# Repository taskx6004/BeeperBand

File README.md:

# BeeperBand

The BeeperBand is an open hardware project to build a minimalist wrist band to notify smartphone message notification with haptic, RGB lights, and interact with physical buttons via BLE connection.

Current prototype intentionally not fitting any display, there are only 3 RGB LEDs, for visual indications. A Linear Haptic Driver can notify user with patterned vibration with minimum audible noise, for non-intrusive usage in various social occasions.

The hardware design is a basically a re-layout PCB of a Adafruit nRF52 Express, to minimize initial firmware development efforts. It also has more sophisticated charger, peripherals required by project specs, and various design decisions for power saving and MCU IO voltage level translations, to utilize software configurable voltage features of nRF52 integrated power converters.

## System Design

nRF52840 is a 2.4GHz RFIC with integrated power converters and flexible IO mapping, with USB2.0 full speed PHY, but has no DFU rom(will brake when no proper firmware present). It can be powered directly with USB host or Li-ion battery, with two stage convert, or single stage convert (skipping first high voltage conversion); two stage conversion could both choose between integrated LDO or buck converter, while buck converter require extra inductors and capacitors to be functional.

To maximize battery life, the BeeperBand implemented two stage buck converter design, all peripheral I/Os have dedicated level translation, and core of nRF52840 works on default 1.8v.

Current stage there’s no functional firmware for BeeperBand hardware (v0.41), all testing is done with Adafruit Feather nRF52840 express bootloader and accompanying BSP and Arduino.

## Peripherals

- 6 GPIO buttons, low-active (enabled when connected to GND)
- 3 x RGB LEDs, SW2812 serial protocol, daisy chained
  - powered by dedicated 3.3V buck converter, with EN pin
  - buck converter is powered by battery
- 1x Linear Haptic Driver
  - dedicated level transfer chip for I2C and GPIO
  - powered by battery, wide voltage range tolerate by level translation
- All unused IO fanned out by 30pin B2B connector
  - with battery output pins
  - 20 IO pins
- 2 LEDs, inherent from Adafruit nRF52840 Feather Express Design
  - RED for Arduino serial activity
  - BLUE for BLE connection activity
  - testing purpose, so the brightness is set to very low (1k resistor on 1.8V IO)

## Charger Circuit

Charger chip is BQ25619 from Texas Instrument with QFN footprint. A WLCSP footprint version is available with part# BQ25618. If PCB size requires further miniaturization, charger and MCU chip can  both replaced with software compatible WLCSP (0.4mm pitch BGA) footprint version.

Like many other BQ chargers from TI, it has a register map for extensive internal controls. But preliminary charging functions does no require MCU control presents. The I/O pins connected to the charger are unused in Feather Express design, so application developer can ignore its presents. To reach 4.2V charge voltage (default 4.1V), and charging current control, a driver firmware is required, and it will work with no intervention to application programs. The power source transition between charging and battery is also seamless, with no program control needed.

BQ chip has 4 power terminals, a little back ground may be helpful in first encounter.

- USB input (VBUS)
  - charge power input
- USB output (PMID)
  - if USB power output as a USB host is required, BQ chip works can work in boost mode to deliver 5V output from battery voltage.
- Battery output (VSYS)
  - Li-ion battery have a minimum voltage required to prevent over discharge, this output will shutdown output to protect battery. If system is overheat, or charge voltage is over-voltage, BQ will also disconnect battery connection.
- Battery input (BAT)
  - This is the dedicated battery connection node. BQ chip has no discharge meter to implement an accurate gas gauge function, but a battery voltage monitor circuit exist in system, to save power this circuit could be shutdown to prevent power leak.

## Testing procedure

PCBA is hand built, this is a long process and require lots of craftsmanship. The SWD port used for upload firmware is not a standard pulg but four small soldering pads, to save space. Fresh nRF52 chip has no per-programmed boot-loader, nor the USB has a hardware DFU mode to boot is from desktop operating system.  To test hardware functionalities, the Adafruit Feather nRF52 Express bootloader is flashed.

Testing procedures are done with Arduino sketches, requires user to upload them separately for each function:

- Buttons
  - not fully implemented due to default Ardruino BSP include only one PIN\_BUTTON(7)
- RGB leds
  - PIN\_NEOPIXEL (8))
- Haptic
  - Requires Adafruit\_DRV2605.h
  - Change writeRegister8(DRV2605\_REG\_OVERDRIVE, 1);
  - call “use\_LRA() in setup()

Currently charger driver is not implemented, but charger I2C communication could be verified.

## Firmware Development

Due to lack of BLE communication software nor data model design, a serial based BLE protocol to manipulate system peripheral called Firmata is recommended to make use cases mock up. During this testing phase, there’s no sophisticated radio power control method could be implemented. This mock up communication firmware will have significant more power consumption than a production firmware, due to communication protocol overhead and onboard program overhead.

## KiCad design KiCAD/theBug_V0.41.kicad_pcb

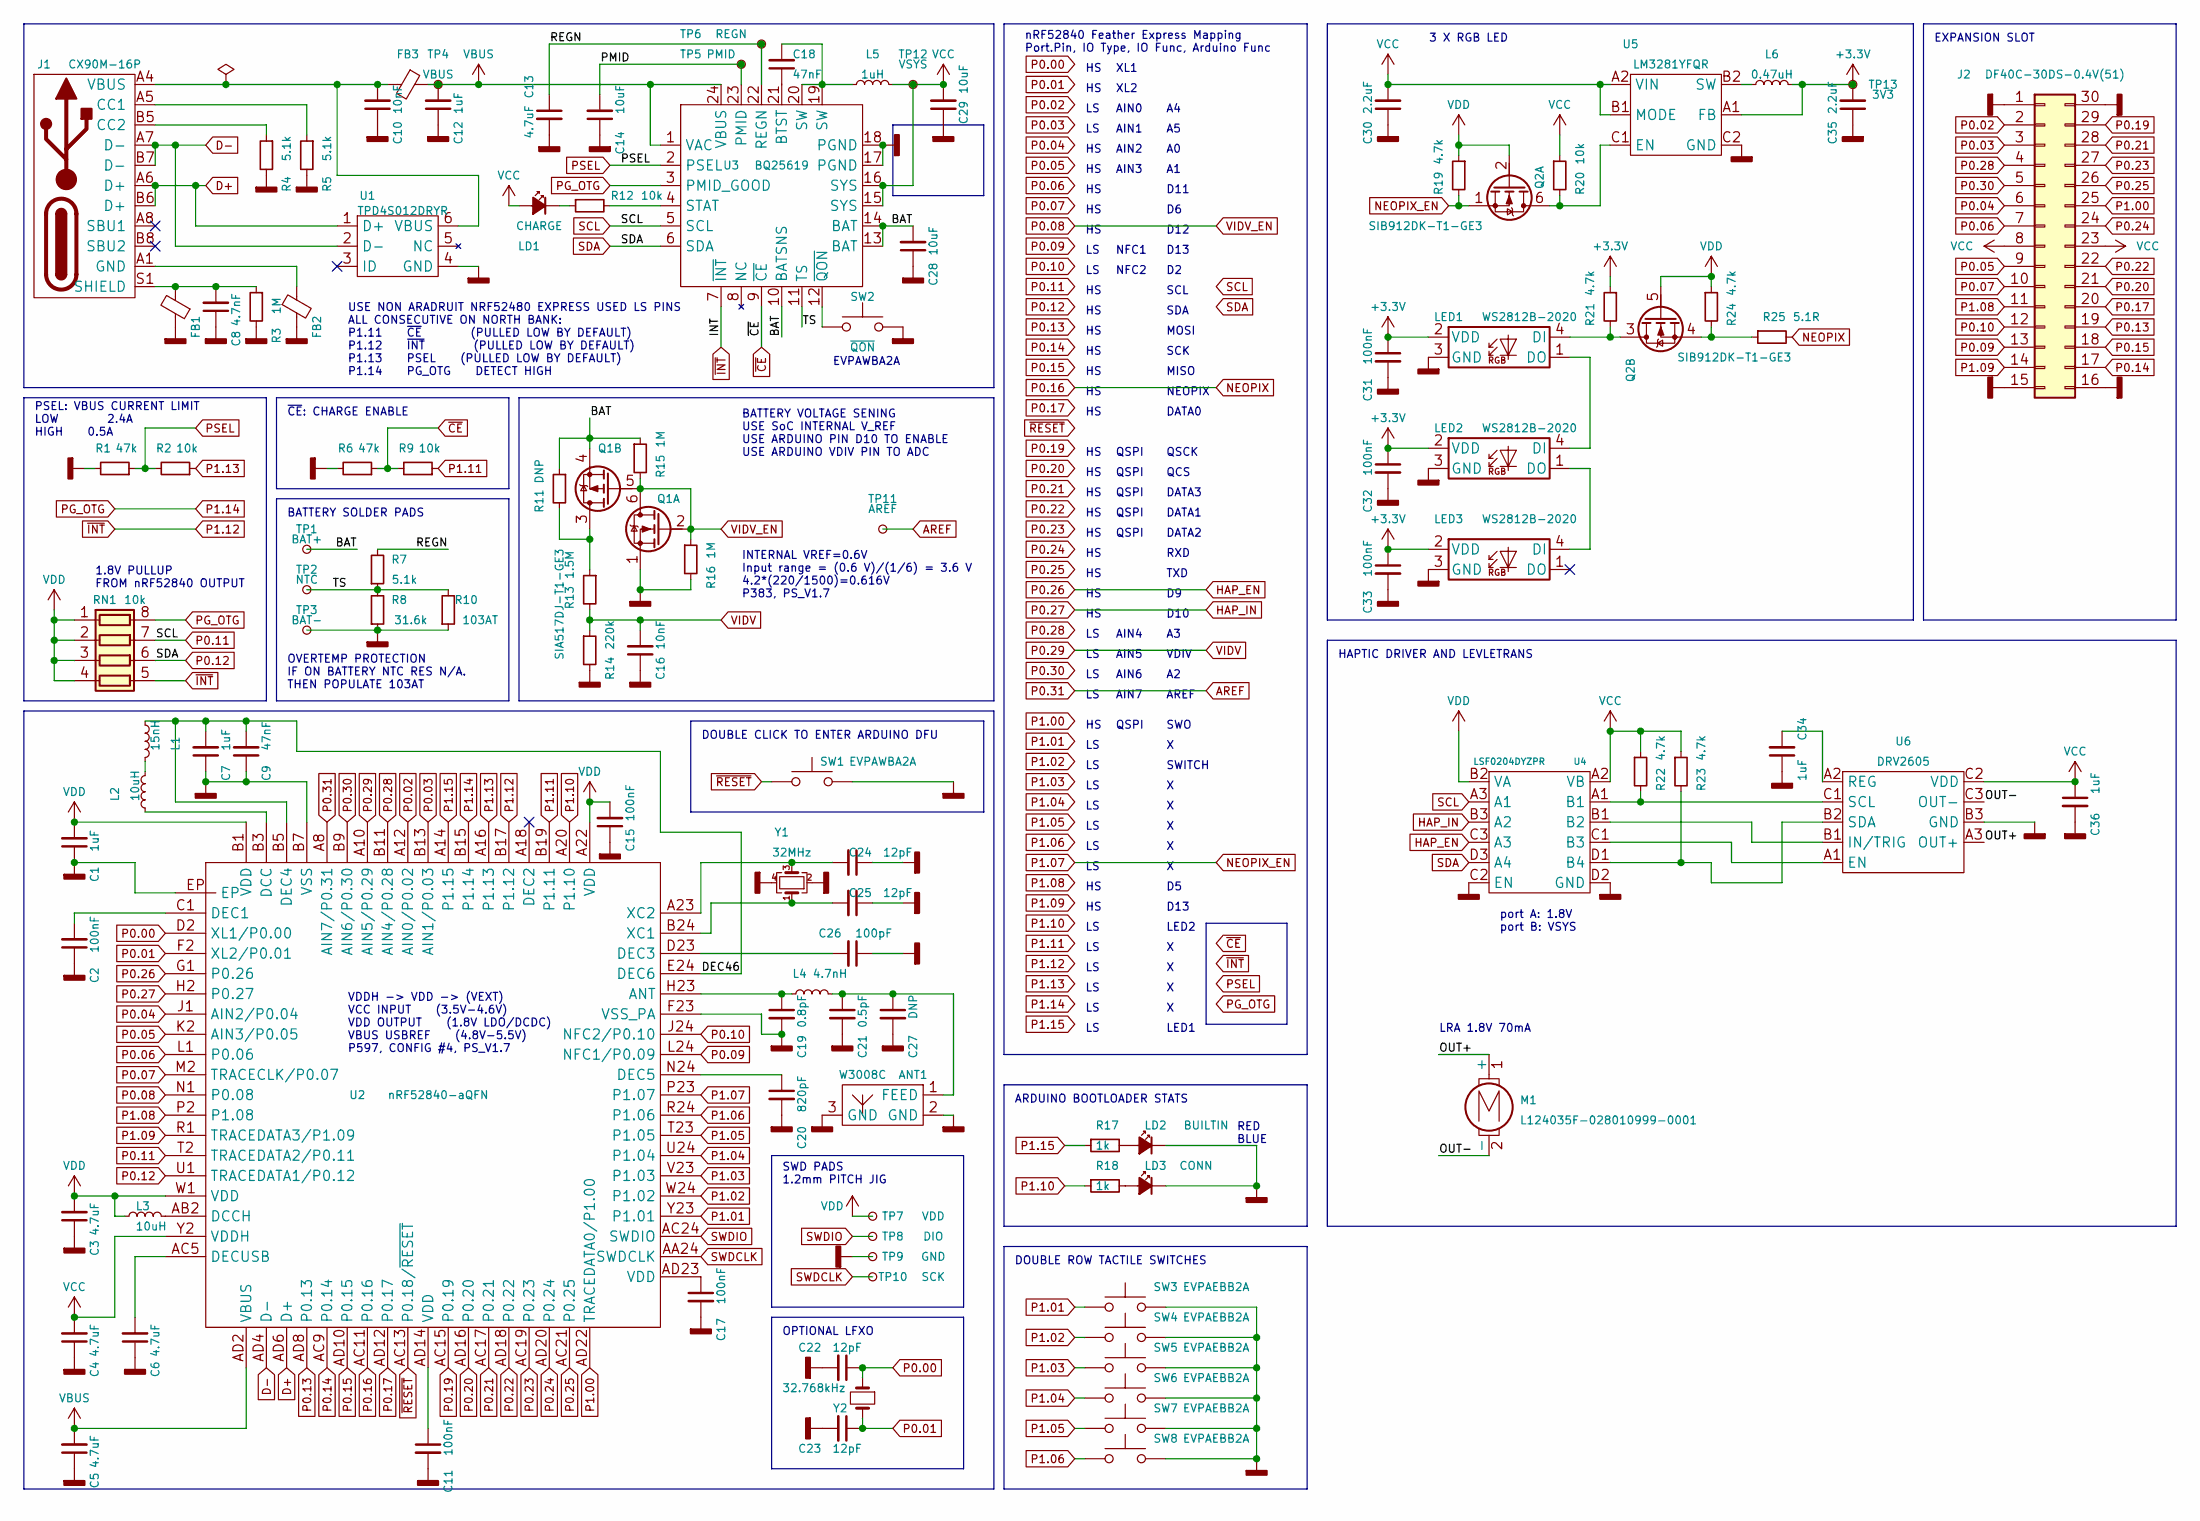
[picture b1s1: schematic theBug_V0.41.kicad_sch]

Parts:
ANT1: W3008C
C1, C7, C12, C34, C36: 1uF; C_0201
C2, C11, C15, C17, C31, C32, C33: 100nF; C_0201
C3, C4, C5, C6, C13: 4.7uF; C_0402_1005Metric
C8: 4.7nF; C_0201
C9, C18: 47nF; C_0201
C10, C16: 10nF; C_0201
C14, C28, C29: 10uF; C_0402_1005Metric
C19: 0.8pF; C_0201
C20: 820pF; C_0201
C21: 0.5pF; C_0201
C22, C23, C24, C25: 12pF; C_0201
C26: 100pF; C_0201
C27: DNP; C_0201
C30, C35: 2.2uF; C_0201
FB1, FB2, FB3: BLM15EX121SN1D; L_0402_1005Metric
J1: CX90M-16P; HRS_CX90M-16P
J2: DF40C-30DS-0.4V(51); DF40C(2.0)-30DS-0.4V(51)
L1: 15nH; L_0201_0603Metric
L2, L3: 10uH; L_0603_1608Metric
L4: 4.7nH; L_0201_0603Metric
L5: 1uH; WIP252010P-1R0ML
L6: 0.47uH; L_0402_1005Metric
LD1: CHARGE; LED_0402
LD2: BUILTIN; LED_0402
LD3: CONN; LED_0402
LED1, LED2, LED3: WS2812B-2020
M1: L124035F-028010999-0001; LL-3-J-27150
Q1: SIA517DJ-T1-GE3; Vishay_PowerPAK_SC70-6L_Dual
Q2: SIB912DK-T1-GE3; Vishay_PowerPAK_SC75-6L_Dual
R1, R6: 47k; R_0201
R2, R9, R12, R20: 10k; R_0201
R3: 1M; R_0402_1005Metric
R4, R5, R7: 5.1k; R_0201
R8: 31.6k; R_0201
R10: 103AT; R_0201
R11: DNP; R_0201
R13: 1.5M; R_0201
R14: 220k; R_0201
R15, R16: 1M; R_0201
R17, R18: 1k; R_0201
R19, R21, R22, R23, R24: 4.7k; R_0201
R25: 5.1R; R_0201
RN1: 10k; R_Array_Convex_4x0402
SW1: EVPAWBA2A
SW2: ~{QON}; EVPAWBA2A
SW3, SW4, SW5, SW6, SW7, SW8: EVPAEBB2A
TP1: BAT+; TestPoint_Pad_D0.6mm
TP2: NTC; TestPoint_Pad_D0.6mm
TP3: BAT-; TestPoint_Pad_D0.6mm
TP4: VBUS; TestPoint_Pad_D0.6mm
TP5: PMID; TestPoint_Pad_D0.6mm
TP6: REGN; TestPoint_Pad_D0.6mm
TP7: VDD; TestPoint_Pad_D0.6mm
TP8: DIO; TestPoint_Pad_D0.6mm
TP9: GND; TestPoint_Pad_D0.6mm
TP10: SCK; TestPoint_Pad_D0.6mm
TP11: AREF; TestPoint_Pad_D0.6mm
TP12: VSYS; TestPoint_Pad_D0.6mm
TP13: 3V3; TestPoint_Pad_D0.6mm
U1: TPD4S012DRYR
U2: nRF52840-aQFN; Nordic_AQFN-73-1EP_7x7mm_P0.5mm
U3: BQ25619
U4: LSF0204DYZPR
U5: LM3281YFQR
U6: DRV2605; DRV2605YZFR
Y1: 32MHz; Crystal_SMD_2016-4Pin_2.0x1.6mm
Y2: 32.768kHz; Crystal_SMD_2012-2Pin_2.0x1.2mm

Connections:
+3.3V: C31.1, C32.1, C33.1, C35.2, L6.2, LED1.2 (VDD), LED2.2 (VDD), LED3.2 (VDD), R21.1, TP13.1, U5.A1 (FB)
/BAT: C28.2, Q1.4, R11.1, R15.1, TP1.1, U3.10 (BATSNS), U3.13 (BAT), U3.14 (BAT)
/DEC46: C7.2, C9.2, L1.2, U2.B5 (DEC4), U2.E24 (DEC6)
/OUT+: M1.1 (+), U6.A3 (OUT+)
/OUT-: M1.2 (-), U6.C3 (OUT-)
/PMID: C14.2, TP5.1, U3.23 (PMID)
/REGN: C13.1, R7.2, TP6.1, U3.22 (REGN)
/TS: R7.1, R8.2, R10.2, TP2.1, U3.11 (TS)
AREF: TP11.1, U2.A8 (AIN7/P0.31)
D+: J1.A6 (D+), J1.B6 (D+), U1.1 (D+), U2.AD6 (D+)
D-: J1.A7 (D-), J1.B7 (D-), U1.2 (D-), U2.AD4 (D-)
GND: ANT1.2 (GND), ANT1.3 (GND), C1.1, C2.1, C3.1, C4.1, C5.1, C6.1, C7.1, C8.1, C9.1, C10.1, C11.2, C12.1, C13.2, C14.1, C15.1, C16.1, C17.2, C19.2, C20.2, C21.2, C22.2, C23.2, C24.1, C25.1, C26.1, C27.2, C28.1, C29.1, C30.1, C31.2, C32.2, C33.2, C34.1, C35.1, C36.2, FB1.1, FB2.2, J2.1, J2.15, J2.16, J2.30, LD2.1 (K), LD3.1 (K), LED1.3 (GND), LED2.3 (GND), LED3.3 (GND), Q1.1, R1.2, R3.2, R4.2, R5.2, R6.2, R8.1, R10.1, R14.2, R16.2, SW1.1, SW2.1, SW3.2, SW4.2, SW5.2, SW6.2, SW7.2, SW8.2, TP3.1, TP9.1, U1.4 (GND), U2.B7 (VSS), U2.EP, U2.F23 (VSS_PA), U3.17 (PGND), U3.18 (PGND), U3.25 (GND), U4.C2 (EN), U4.D2 (GND), U5.C2 (GND), U6.B3 (GND), Y1.2, Y1.4
HAP_EN: U2.G1 (P0.26), U4.C3 (A3)
HAP_IN: U2.H2 (P0.27), U4.B3 (A2)
NEOPIX: R25.2, U2.AC11 (P0.16)
NEOPIX_EN: Q2.1, R19.2, U2.P23 (P1.07)
unnamed: ANT1.1 (FEED), C21.1, C27.1, L4.2
unnamed: C2.2, U2.C1 (DEC1)
unnamed: C6.2, U2.AC5 (DECUSB)
unnamed: C8.2, FB1.2, J1.S1 (SHIELD), R3.1
unnamed: C10.2, FB3.2, J1.A4 (VBUS), J1.A9 (VBUS), J1.B4 (VBUS), J1.B9 (VBUS), U1.6 (VBUS)
unnamed: C11.1, U2.AD14 (VDD)
unnamed: C17.1, U2.AD23 (VDD)
unnamed: C18.1, U3.21 (BTST)
unnamed: C18.2, L5.1, U3.19 (SW), U3.20 (SW)
unnamed: C19.1, L4.1, U2.H23 (ANT)
unnamed: C20.1, U2.N24 (DEC5)
unnamed: C24.2, U2.A23 (XC2), Y1.3
unnamed: C25.2, U2.B24 (XC1), Y1.1
unnamed: C26.2, U2.D23 (DEC3)
unnamed: C34.2, U6.A2 (REG)
unnamed: FB2.1, J1.A1 (GND), J1.A12 (GND), J1.B1 (GND), J1.B12 (GND)
unnamed: J1.A5 (CC1), R5.1
unnamed: J1.B5 (CC2), R4.1
unnamed: L1.1, L2.2
unnamed: L2.1, U2.B3 (DCC)
unnamed: L3.2, U2.AB2 (DCCH)
unnamed: L6.1, U5.B2 (SW)
unnamed: LD1.1 (K), R12.1
unnamed: LD2.2 (A), R17.2
unnamed: LD3.2 (A), R18.2
unnamed: LED1.1 (DO), LED2.4 (DI)
unnamed: LED1.4 (DI), Q2.3, R21.2
unnamed: LED2.1 (DO), LED3.4 (DI)
unnamed: Q1.3, R11.2, R13.1
unnamed: Q2.4, R24.2, R25.1
unnamed: Q2.6, R20.2, U5.C1 (EN)
unnamed: R12.2, U3.4 (STAT)
unnamed: R22.2, U4.A1 (B1), U6.C1 (SCL)
unnamed: R23.2, U4.D1 (B4), U6.B2 (SDA)
unnamed: SW2.2, U3.12 (~QON)
unnamed: U4.B1 (B2), U6.B1 (IN/TRIG)
unnamed: U4.C1 (B3), U6.A1 (EN)
P0.00: C22.1, U2.D2 (XL1/P0.00), Y2.1
P0.01: C23.1, U2.F2 (XL2/P0.01), Y2.2
P0.02: J2.2, U2.A12 (AIN0/P0.02)
P0.03: J2.3, U2.B13 (AIN1/P0.03)
P0.04: J2.6, U2.J1 (AIN2/P0.04)
P0.05: J2.9, U2.K2 (AIN3/P0.05)
P0.06: J2.7, U2.L1 (P0.06)
P0.07: J2.10, U2.M2 (TRACECLK/P0.07)
P0.08: Q1.2, Q1.5, Q1.6, R15.2, R16.1, U2.N1 (P0.08)
P0.09: J2.13, U2.L24 (NFC1/P0.09)
P0.10: J2.12, U2.J24 (NFC2/P0.10)
P0.11: RN1.7 (R2.2), U2.T2 (TRACEDATA2/P0.11), U3.5 (SCL), U4.A3 (A1)
P0.12: RN1.6 (R3.2), U2.U1 (TRACEDATA1/P0.12), U3.6 (SDA), U4.D3 (A4)
P0.13: J2.19, U2.AD8 (P0.13)
P0.14: J2.17, U2.AC9 (P0.14)
P0.15: J2.18, U2.AD10 (P0.15)
P0.17: J2.20, U2.AD12 (P0.17)
P0.19: J2.29, U2.AC15 (P0.19)
P0.20: J2.21, U2.AD16 (P0.20)
P0.21: J2.28, U2.AC17 (P0.21)
P0.22: J2.22, U2.AD18 (P0.22)
P0.23: J2.27, U2.AC19 (P0.23)
P0.24: J2.24, U2.AD20 (P0.24)
P0.25: J2.26, U2.AC21 (P0.25)
P0.28: J2.4, U2.B11 (AIN4/P0.28)
P0.29: C16.2, R13.2, R14.1, U2.A10 (AIN5/P0.29)
P0.30: J2.5, U2.B9 (AIN6/P0.30)
P1.00: J2.25, U2.AD22 (TRACEDATA0/P1.00)
P1.01: SW3.1, U2.Y23 (P1.01)
P1.02: SW4.1, U2.W24 (P1.02)
P1.03: SW5.1, U2.V23 (P1.03)
P1.04: SW6.1, U2.U24 (P1.04)
P1.05: SW7.1, U2.T23 (P1.05)
P1.06: SW8.1, U2.R24 (P1.06)
P1.08: J2.11, U2.P2 (P1.08)
P1.09: J2.14, U2.R1 (TRACEDATA3/P1.09)
P1.10: R18.1, U2.A20 (P1.10)
P1.11: R9.1, U2.B19 (P1.11)
P1.12: RN1.5 (R4.2), U2.B17 (P1.12), U3.7 (~INT)
P1.13: R2.1, U2.A16 (P1.13)
P1.14: RN1.8 (R1.2), U2.B15 (P1.14), U3.3 (PMID_GOOD)
P1.15: R17.1, U2.A14 (P1.15)
PSEL: R1.1, R2.2, U3.2 (PSEL)
SWDCLK: TP10.1, U2.AA24 (SWDCLK)
SWDIO: TP8.1, U2.AC24 (SWDIO)
VBUS: C5.2, C12.2, FB3.1, TP4.1, U2.AD2 (VBUS), U3.1 (VAC), U3.24 (VBUS)
VCC: C4.2, C29.2, C30.2, C36.1, J2.8, J2.23, L5.2, LD1.2 (A), R20.1, R22.1, R23.1, TP12.1, U2.Y2 (VDDH), U3.15 (SYS), U3.16 (SYS), U4.A2 (VB), U5.A2 (VIN), U5.B1 (MODE), U6.C2 (VDD)
VDD: C1.2, C3.2, C15.2, L3.1, Q2.2, Q2.5, R19.1, R24.1, RN1.1 (R1.1), RN1.2 (R2.1), RN1.3 (R3.1), RN1.4 (R4.1), TP7.1, U2.A22 (VDD), U2.B1 (VDD), U2.W1 (VDD), U4.B2 (VA)
~CE: R6.1, R9.2, U3.9 (~CE)
~RESET: SW1.2, U2.AC13 (P0.18/~RESET)

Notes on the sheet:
USE NON ARADRUIT NRF52480 EXPRESS USED LS PINS ALL CONSECUTIVE ON NORTH BANK: P1.11 ~{CE} (PULLED LOW BY DEFAULT) P1.12 ~{INT} (PULLED LOW BY DEFAULT) P1.13 PSEL (PULLED LOW BY DEFAULT) P1.14 PG_OTG DETECT HIGH
HAPTIC DRIVER AND LEVLETRANS
DATA1
QCS
LRA 1.8V 70mA
QSPI
DATA3
DATA2
D13
OPTIONAL LFXO
NEOPIX
ARDUINO BOOTLOADER STATS
MOSI
INTERNAL VREF=0.6V Input range = (0.6 V)/(1/6) = 3.6 V 4.2*(220/1500)=0.616V P383, PS_V1.7
nRF52840 Feather Express Mapping Port.Pin, IO Type, IO Func, Arduino Func
LED1
SWITCH
XL1
TXD
AIN6
EVPAWBA2A
AIN0
AIN3
PSEL: VBUS CURRENT LIMIT LOW 2.4A HIGH 0.5A
DOUBLE CLICK TO ENTER ARDUINO DFU
NFC1
DOUBLE ROW TACTILE SWITCHES
1.8V PULLUP FROM nRF52840 OUTPUT
AIN1
QSCK
DATA0
~{CE}: CHARGE ENABLE
VDDH -> VDD -> (VEXT) VCC INPUT (3.5V-4.6V) VDD OUTPUT (1.8V LDO/DCDC) VBUS USBREF (4.8V-5.5V) P597, CONFIG #4, PS_V1.7
RXD
AIN5
AREF
D11
AIN7
BATTERY SOLDER PADS
AIN4

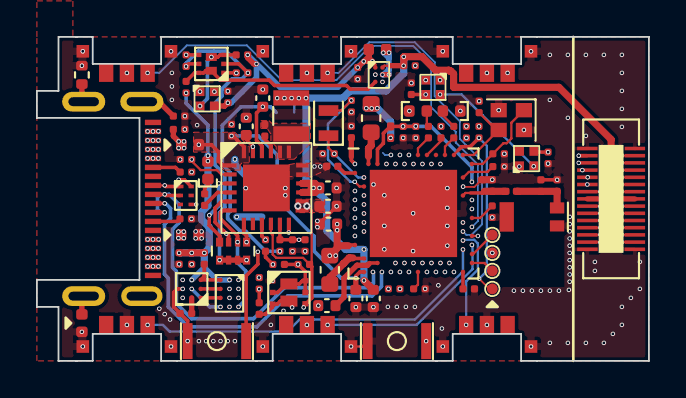
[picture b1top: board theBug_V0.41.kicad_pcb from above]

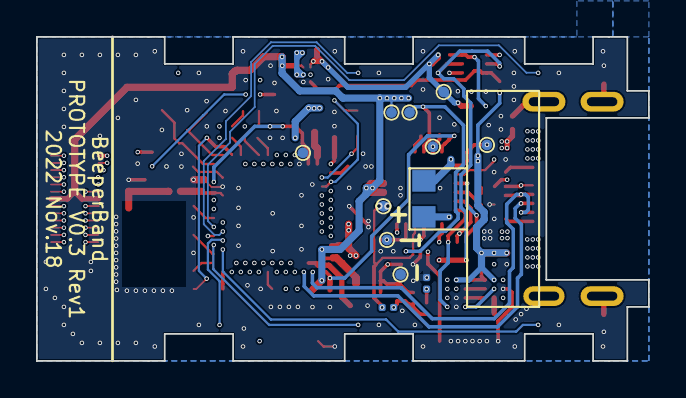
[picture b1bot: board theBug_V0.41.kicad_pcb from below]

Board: 4 copper layers, 34.0 x 18.0 mm, 112 parts (12 on the bottom side), 103 nets.

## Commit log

2023-03-23 Create BeeperBand_SCH_V0.41.pdf
    Add PDF schematic
2023-03-24 initial documents upload
2023-03-24 add BeeperBand Firmware Dev 101 readme
